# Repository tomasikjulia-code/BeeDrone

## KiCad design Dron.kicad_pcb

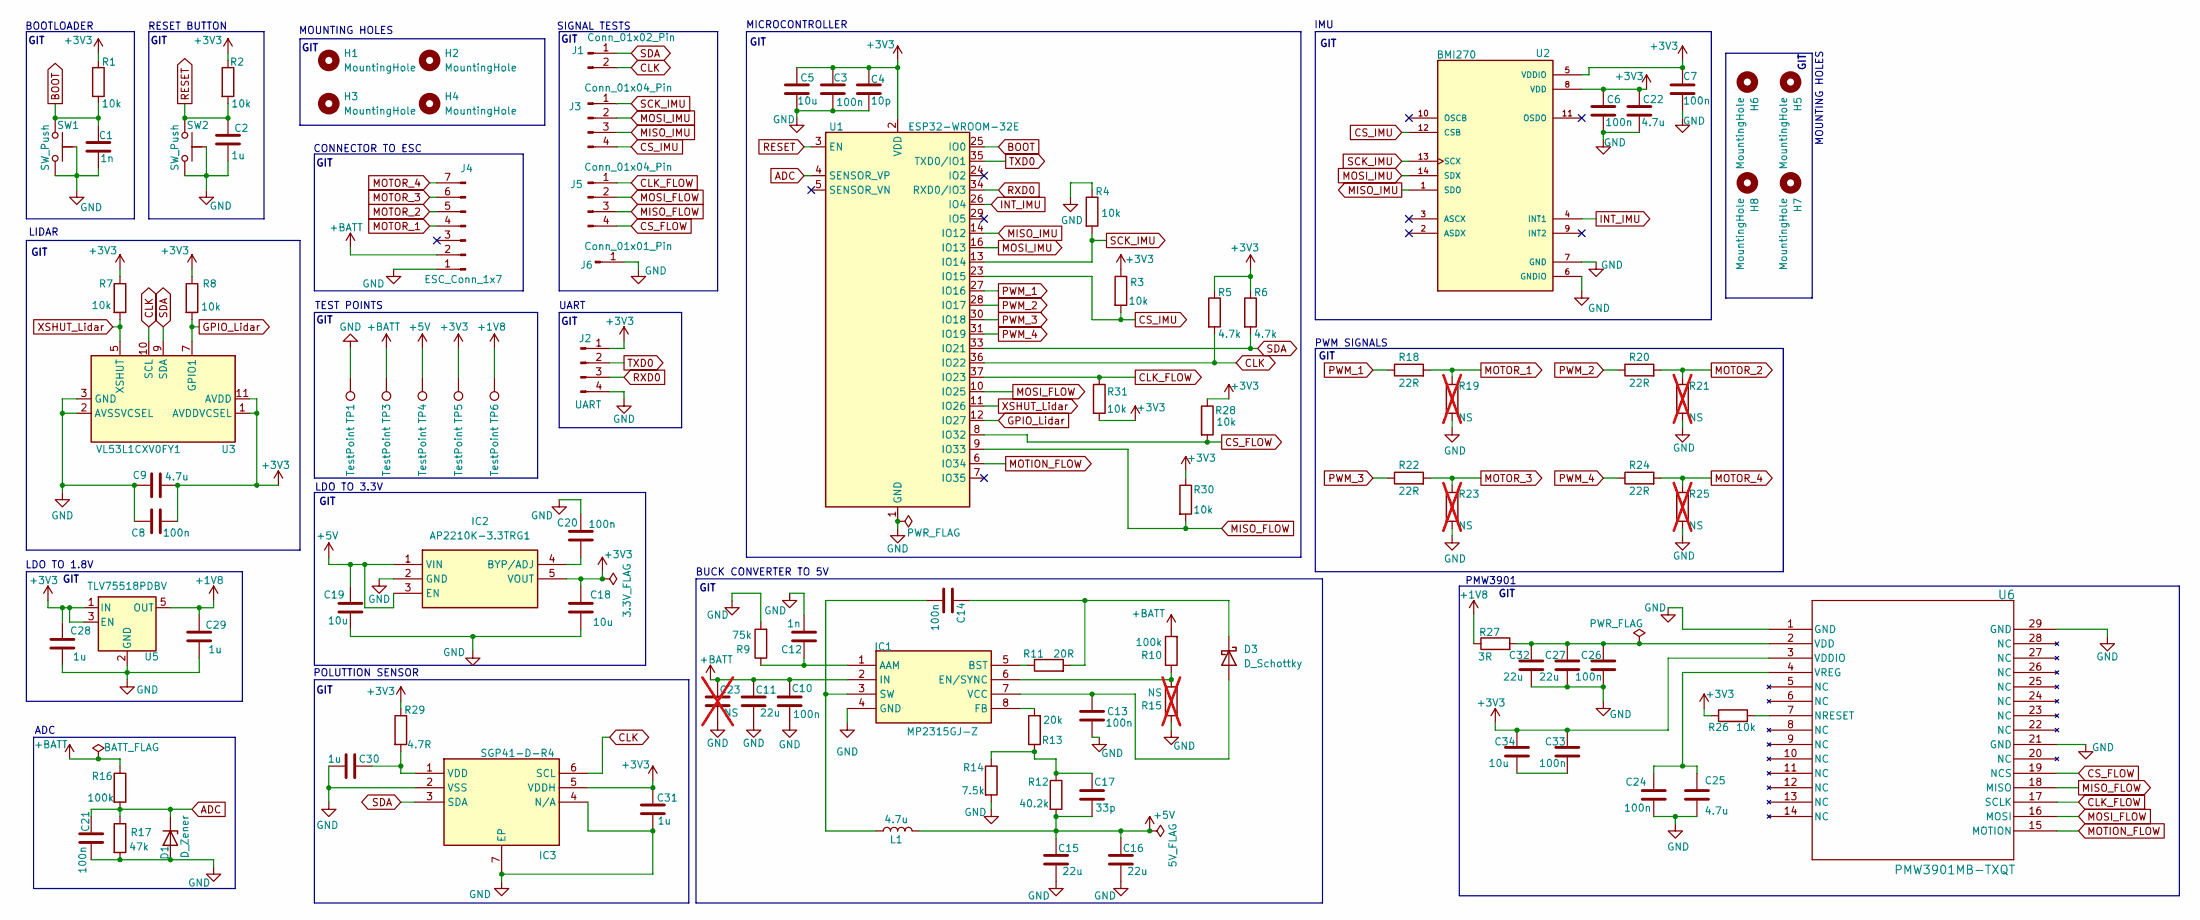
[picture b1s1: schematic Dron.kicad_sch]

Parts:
C1, C12: 1n; C_0402_1005Metric_Pad0.74x0.62mm_HandSolder
C2, C28, C29, C30, C31: 1u; C_0402_1005Metric_Pad0.74x0.62mm_HandSolder
C3, C6, C7, C8, C10, C13, C14, C20, C21, C24, C26, C33: 100n; C_0402_1005Metric_Pad0.74x0.62mm_HandSolder
C4: 10p; C_0402_1005Metric_Pad0.74x0.62mm_HandSolder
C5, C18, C19, C34: 10u; C_0402_1005Metric_Pad0.74x0.62mm_HandSolder
C9, C22, C25: 4.7u; C_0603_1608Metric_Pad1.08x0.95mm_HandSolder
C11: 22u; C_0805_2012Metric_Pad1.18x1.45mm_HandSolder
C15, C16, C27, C32: 22u; C_0603_1608Metric_Pad1.08x0.95mm_HandSolder
C17: 33p; C_0402_1005Metric_Pad0.74x0.62mm_HandSolder
C23: NS; C_0402_1005Metric_Pad0.74x0.62mm_HandSolder; not fitted
D1: D_Zener; D_SOD-123F
D3: D_Schottky; D_SOD-323F
H1, H2, H3, H4: MountingHole; MountingHole_2.7mm_M2.5_DIN965_Pad
H5, H6, H7, H8: MountingHole; MountingHole_2.2mm_M2_DIN965_Pad
IC1: MP2315GJ-Z; SOT65P280X100-8N; Mouser Part Number 946-MP2315GJZ
IC2: AP2210K-3.3TRG1; SOT95P282X145-5N; Manufacturer_Part_Number AP2210K-3.3TRG1
IC3: SGP41-D-R4; SON80P244X244X95-7N; Mouser Part Number 403-SGP41-D-R4
J1: Conn_01x02_Pin; PinHeader_1x02_P2.00mm_Vertical
J2: UART; PinHeader_1x04_P2.54mm_Vertical
J3, J5: Conn_01x04_Pin; PinHeader_1x04_P2.00mm_Vertical
J4: ESC_Conn_1x7; PinHeader_1x07_P2.00mm_Vertical_JULA
J6: Conn_01x01_Pin; PinHeader_1x01_P2.00mm_Vertical
L1: 4.7u; L_Taiyo-Yuden_NR-50xx
R1, R2, R3, R4, R7, R8, R26, R28, R30, R31: 10k; R_0402_1005Metric_Pad0.72x0.64mm_HandSolder
R5, R6: 4.7k; R_0402_1005Metric_Pad0.72x0.64mm_HandSolder
R9: 75k; R_0402_1005Metric_Pad0.72x0.64mm_HandSolder
R10, R16: 100k; R_0402_1005Metric_Pad0.72x0.64mm_HandSolder
R11: 20R; R_0402_1005Metric_Pad0.72x0.64mm_HandSolder
R12: 40.2k; R_0402_1005Metric_Pad0.72x0.64mm_HandSolder
R13: 20k; R_0402_1005Metric_Pad0.72x0.64mm_HandSolder
R14: 7.5k; R_0402_1005Metric_Pad0.72x0.64mm_HandSolder
R15, R19, R21, R23, R25: NS; R_0402_1005Metric_Pad0.72x0.64mm_HandSolder; not fitted
R17: 47k; R_0402_1005Metric_Pad0.72x0.64mm_HandSolder
R18, R20, R22, R24: 22R; R_0402_1005Metric_Pad0.72x0.64mm_HandSolder
R27: 3R; R_0402_1005Metric_Pad0.72x0.64mm_HandSolder
R29: 4.7R; R_0402_1005Metric_Pad0.72x0.64mm_HandSolder
SW1, SW2: SW_Push; SW_Push_1P1T-SH_NO_CK_KMR2xxG
TP1, TP3, TP4, TP5, TP6: TestPoint; TestPoint_Pad_D1.5mm
U1: ESP32-WROOM-32E
U2: BMI270; XDCR_BMI270
U3: VL53L1CXV0FY1; ST_VL53L1x
U5: TLV75518PDBV; SOT-23-5
U6: PMW3901MB-TXQT; QFN_01MB-TXQT_PIX

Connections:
+1V8: C29.1, R27.1, TP6.1, U5.5 (OUT)
+3V3: C3.1, C4.1, C5.1, C6.1, C7.1, C8.2, C9.2, C18.1, C22.1, C28.1, C31.2, C33.1, C34.1, IC2.5 (VOUT), IC3.5 (VDDH), J2.1, R1.1, R2.1, R3.1, R5.1, R6.1, R7.1, R8.1, R26.1, R28.1, R29.1, R30.1, R31.2, TP5.1, U1.2 (VDD), U2.5 (VDDIO), U2.8 (VDD), U3.1 (AVDDVCSEL), U3.11 (AVDD), U5.1 (IN), U5.3 (EN), U6.3 (VDDIO)
+5V: C15.1, C16.1, C17.2, C19.1, IC2.1 (VIN), IC2.3 (EN), L1.2, R12.2, TP4.1
+BATT: C10.1, C11.1, C23.1, IC1.2 (IN), J4.2, R10.2, R16.1, TP3.1
ADC: C21.1, D1.1 (K), R16.2, R17.1, U1.4 (SENSOR_VP)
BOOT: C1.1, R1.2, SW1.1, U1.25 (IO0)
CLK: IC3.6 (SCL), J1.2, R5.2, U1.36 (IO22), U3.10 (SCL)
CLK_FLOW: J5.1, R31.1, U1.37 (IO23), U6.17 (SCLK)
CS_FLOW: J5.4, R28.2, U1.8 (IO32), U6.19 (NCS)
CS_IMU: J3.4, R3.2, U1.23 (IO15), U2.12 (CSB)
GND: C1.2, C2.2, C3.2, C4.2, C5.2, C6.2, C7.2, C8.1, C9.1, C10.2, C11.2, C12.2, C13.2, C15.2, C16.2, C18.2, C19.2, C20.1, C21.2, C22.2, C23.2, C24.2, C25.2, C26.2, C27.2, C28.2, C29.2, C30.1, C31.1, C32.2, D1.2 (A), IC1.4 (GND), IC2.2 (GND), IC3.2 (VSS), IC3.4 (N/A), IC3.7 (EP), J2.4, J4.1, J6.1, R4.1, R9.2, R14.2, R15.1, R17.2, R19.2, R21.2, R23.2, R25.2, SW1.2, SW1.SH, SW2.2, SW2.SH, TP1.1, U1.1 (GND), U1.15 (GND), U1.38 (GND), U1.39 (GND), U2.6 (GNDIO), U2.7 (GND), U3.2 (AVSSVCSEL), U3.3 (GND), U3.4 (GND), U3.6 (GND), U3.12 (GND), U5.2 (GND), U6.1 (GND), U6.21 (GND), U6.29 (GND)
GPIO_Lidar: R8.2, U1.12 (IO27), U3.7 (GPIO1)
INT_IMU: U1.26 (IO4), U2.4 (INT1)
MISO_FLOW: J5.3, R30.2, U1.9 (IO33), U6.18 (MISO)
MISO_IMU: J3.3, U1.14 (IO12), U2.1 (SDO)
MOSI_FLOW: J5.2, U1.10 (IO25), U6.16 (MOSI)
MOSI_IMU: J3.2, U1.16 (IO13), U2.14 (SDX)
MOTION_FLOW: U1.6 (IO34), U6.15 (MOTION)
MOTOR_1: J4.4, R18.2, R19.1
MOTOR_2: J4.5, R20.2, R21.1
MOTOR_3: J4.6, R22.2, R23.1
MOTOR_4: J4.7, R24.2, R25.1
unnamed: C17.1, R12.1, R13.1, R14.1
unnamed: C33.2, C34.2
unnamed: C13.1, D3.2 (A), IC1.7 (VCC)
unnamed: C14.1, D3.1 (K), R11.2
unnamed: C12.1, IC1.1 (AAM), R9.1
unnamed: IC1.5 (BST), R11.1
unnamed: IC1.6 (EN/SYNC), R10.1, R15.2
unnamed: IC1.8 (FB), R13.2
unnamed: C14.2, IC1.3 (SW), L1.1
unnamed: C20.2, IC2.4 (BYP/ADJ)
unnamed: C30.2, IC3.1 (VDD), R29.2
unnamed: R26.2, U6.7 (NRESET)
unnamed: C26.1, C27.1, C32.1, R27.2, U6.2 (VDD)
unnamed: C24.1, C25.1, U6.4 (VREG)
PWM_1: R18.1, U1.27 (IO16)
PWM_2: R20.1, U1.28 (IO17)
PWM_3: R22.1, U1.30 (IO18)
PWM_4: R24.1, U1.31 (IO19)
RESET: C2.1, R2.2, SW2.1, U1.3 (EN)
RXD0: J2.3, U1.34 (RXD0/IO3)
SCK_IMU: J3.1, R4.2, U1.13 (IO14), U2.13 (SCX)
SDA: IC3.3 (SDA), J1.1, R6.2, U1.33 (IO21), U3.9 (SDA)
TXD0: J2.2, U1.35 (TXD0/IO1)
XSHUT_Lidar: R7.2, U1.11 (IO26), U3.5 (XSHUT)

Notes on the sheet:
GIT
LDO TO 1.8V
BUCK CONVERTER TO 5V
MICROCONTROLLER
MOUNTING HOLES
SIGNAL TESTS
POLUTTION SENSOR
PMW3901
TEST POINTS
IMU
PWM SIGNALS
LIDAR
CONNECTOR TO ESC
ADC
LDO TO 3.3V
RESET BUTTON
UART
BOOTLOADER

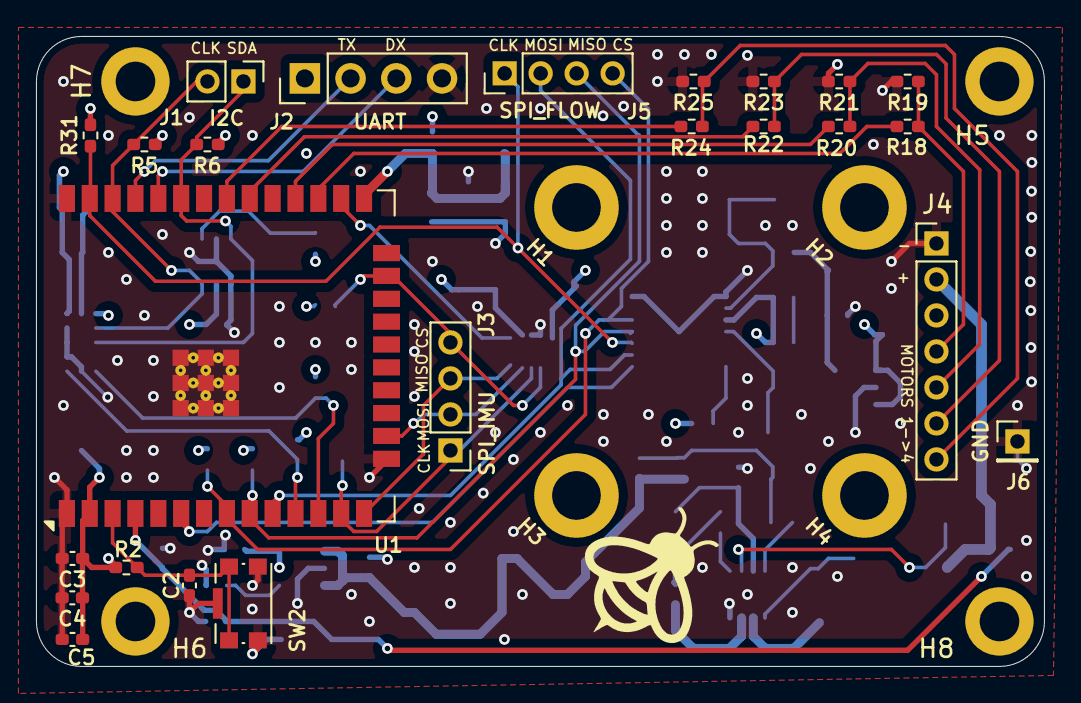
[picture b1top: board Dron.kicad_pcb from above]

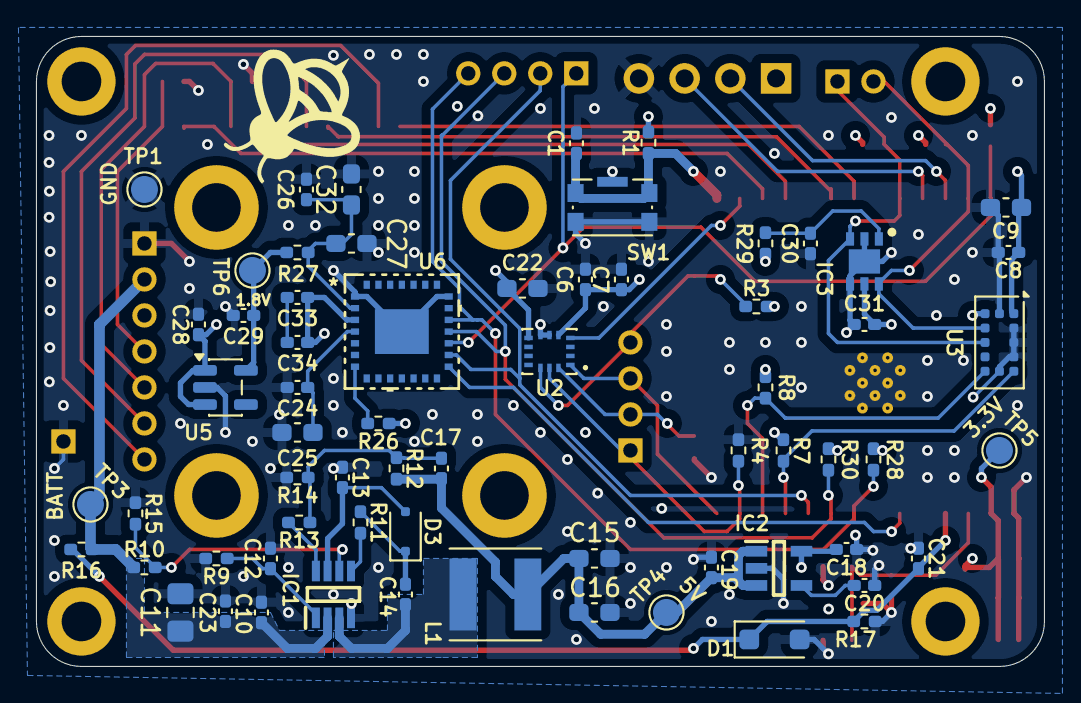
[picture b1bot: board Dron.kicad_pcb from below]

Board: 4 copper layers, 56.0 x 35.0 mm, 97 parts (65 on the bottom side), 46 nets.
